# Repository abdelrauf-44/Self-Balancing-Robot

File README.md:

# 🤖 Self-Balancing Robot (ESP32 + MPU6050)

A two-wheeled self-balancing robot based on ESP32 and MPU6050 IMU, implementing PID control to stabilize an inverted pendulum system in real time.
The project focuses on practical control engineering, embedded systems, and electromechanical integration.

# 📌 Project Overview

This project demonstrates the design and implementation of a self-balancing robot using:

Real-time sensor fusion for tilt angle estimation

Closed-loop PID control for balance stabilization

PWM-based DC motor control

Embedded implementation on an ESP32 microcontroller

The robot is capable of maintaining an upright position and recovering from small disturbances.

# 🧩 System Architecture

Main subsystems:

Sensing: MPU6050 (accelerometer + gyroscope)

Control: PID controller running on ESP32

Actuation: Dual DC motors via motor driver

Power: Battery supply with onboard 5V regulation for the motor driver

# 🛠️ Hardware Components

ESP32 super mini 

MPU6050 IMU

DC  Motors (2×)

Motor Driver (L293D)

3D-printed mechanical frame

Battery pack with power switch

# 🔌 Electrical Schematic

The schematic below shows the complete electrical design including:

Power regulation stage

ESP32 GPIO connections

Motor driver interface

# 🧱 Mechanical Design & Assembly

# 🎯 Control Strategy
Angle Estimation

MPU6050 accelerometer and gyroscope data are combined to estimate the robot tilt angle.

Gyroscope data provides short-term accuracy, while accelerometer data corrects long-term drift.

# PID Controller

The controller minimizes the tilt angle error using:

Proportional (P): Immediate correction based on angle error

Integral (I): Reduces steady-state error

Derivative (D): Improves damping and stability

Controller output is converted to PWM signals driving the motors.

# 💻 Software Architecture

Platform: Arduino framework (ESP32)

Main loop:

Read IMU data

Compute tilt angle

Apply PID control

Update motor PWM outputs

Modular structure for easy tuning and testing

# 📡 Features

Real-time balance stabilization

Adjustable PID parameters

Compact embedded implementation

# 🧪 Results & Observations

The robot can balance successfully for short to medium durations.

System stability is sensitive to:

PID tuning

Sensor noise and drift

Loop timing consistency

The project highlights real-world control challenges beyond simulation.

# 🚀 Future Improvements

Implement complementary or Kalman filtering

Add encoder feedback for velocity control

Improve mechanical rigidity

Implement auto-tuning or adaptive control

Wireless parameter tuning and monitoring

# ▶️ How to Run

Upload the firmware to the ESP32 using Arduino IDE

Power the robot on a flat surface

Tune PID parameters carefully

Gradually test balance recovery

⚠️ Start with low motor speed limits to avoid damage.

# 👤 Author

Mohamed Abdelrauf
Electrcial Engineering (UTM) 
Self-Balancing Robot Project

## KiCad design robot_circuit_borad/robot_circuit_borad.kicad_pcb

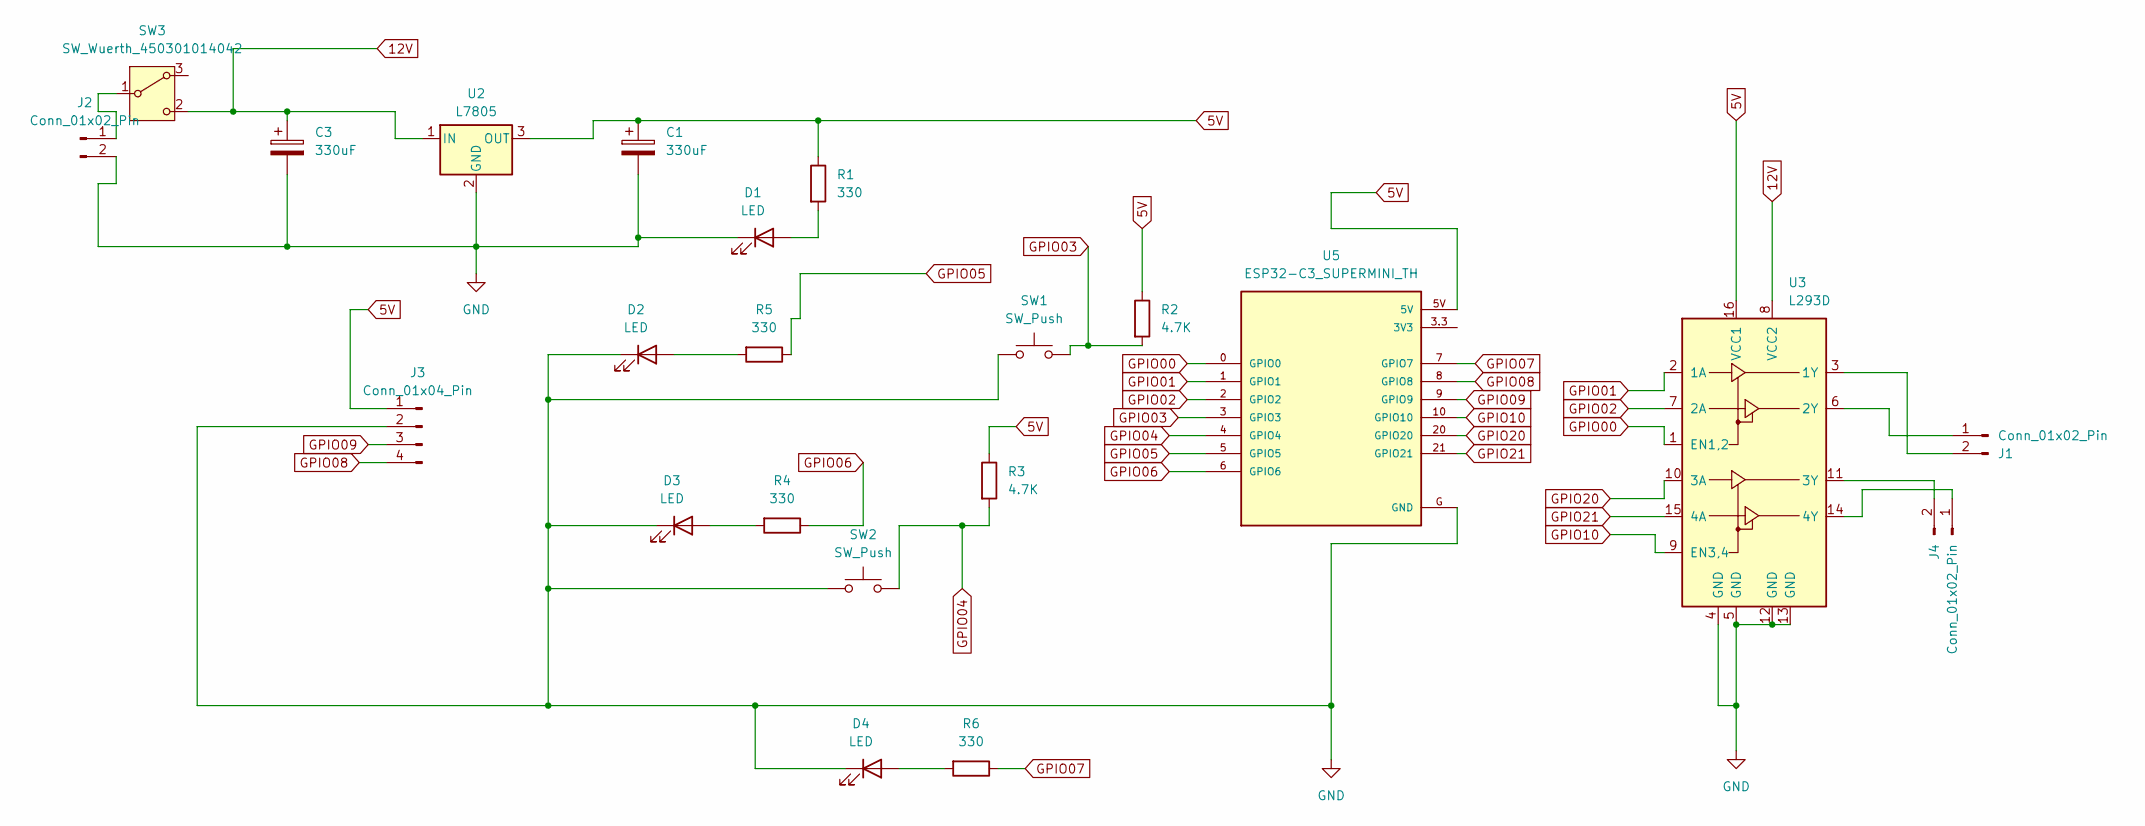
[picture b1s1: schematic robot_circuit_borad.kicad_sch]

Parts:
C1, C3: 330uF; CP_Radial_D6.3mm_P2.50mm
D1, D2, D3, D4: LED; LED_D3.0mm
J1, J2, J4: Conn_01x02_Pin; JST_XH_B2B-XH-A_1x02_P2.50mm_Vertical
J3: Conn_01x04_Pin; PinHeader_1x04_P2.54mm_Vertical
R1, R4, R5, R6: 330; R_Axial_DIN0207_L6.3mm_D2.5mm_P10.16mm_Horizontal
R2, R3: 4.7K; R_Axial_DIN0207_L6.3mm_D2.5mm_P10.16mm_Horizontal
SW1, SW2: SW_Push; SW_TH_Tactile_Omron_B3F-10xx
SW3: SW_Wuerth_450301014042; SW_Slide-03_Wuerth-WS-SLTV_10x2.5x6.4_P2.54mm
U2: L7805; TO-220-3_Vertical
U3: L293D; DIP-16_W7.62mm
U5: ESP32-C3_SUPERMINI_TH; MODULE_ESP32-C3_SUPERMINI

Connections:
5V: C1.1, J3.1, R1.1, R2.1, R3.1, U2.3 (OUT), U3.16 (VCC1), U5.5V
12V: C3.1, SW3.2 (C), U2.1 (IN), U3.8 (VCC2)
GND: C1.2, C3.2, D1.1 (K), D2.1 (K), D3.1 (K), D4.1 (K), J2.2, J3.2, SW1.1, SW2.1, U2.2 (GND), U3.4 (GND), U3.5 (GND), U3.12 (GND), U3.13 (GND), U5.G (GND)
GPIO00: U3.1 (EN1,2), U5.0 (GPIO0)
GPIO01: U3.2 (1A), U5.1 (GPIO1)
GPIO02: U3.7 (2A), U5.2 (GPIO2)
GPIO03: R2.2, SW1.2, U5.3 (GPIO3)
GPIO04: R3.2, SW2.2, U5.4 (GPIO4)
GPIO05: R5.1, U5.5 (GPIO5)
GPIO06: R4.1, U5.6 (GPIO6)
GPIO07: R6.1, U5.7 (GPIO7)
GPIO08: J3.4, U5.8 (GPIO8)
GPIO09: J3.3, U5.9 (GPIO9)
GPIO10: U3.9 (EN3,4), U5.10 (GPIO10)
GPIO20: U3.10 (3A), U5.20 (GPIO20)
GPIO21: U3.15 (4A), U5.21 (GPIO21)
unnamed: D1.2 (A), R1.2
unnamed: D2.2 (A), R5.2
unnamed: D3.2 (A), R4.2
unnamed: D4.2 (A), R6.2
unnamed: J1.1, U3.6 (2Y)
unnamed: J1.2, U3.3 (1Y)
unnamed: J2.1, SW3.1 (B)
unnamed: J4.1, U3.14 (4Y)
unnamed: J4.2, U3.11 (3Y)

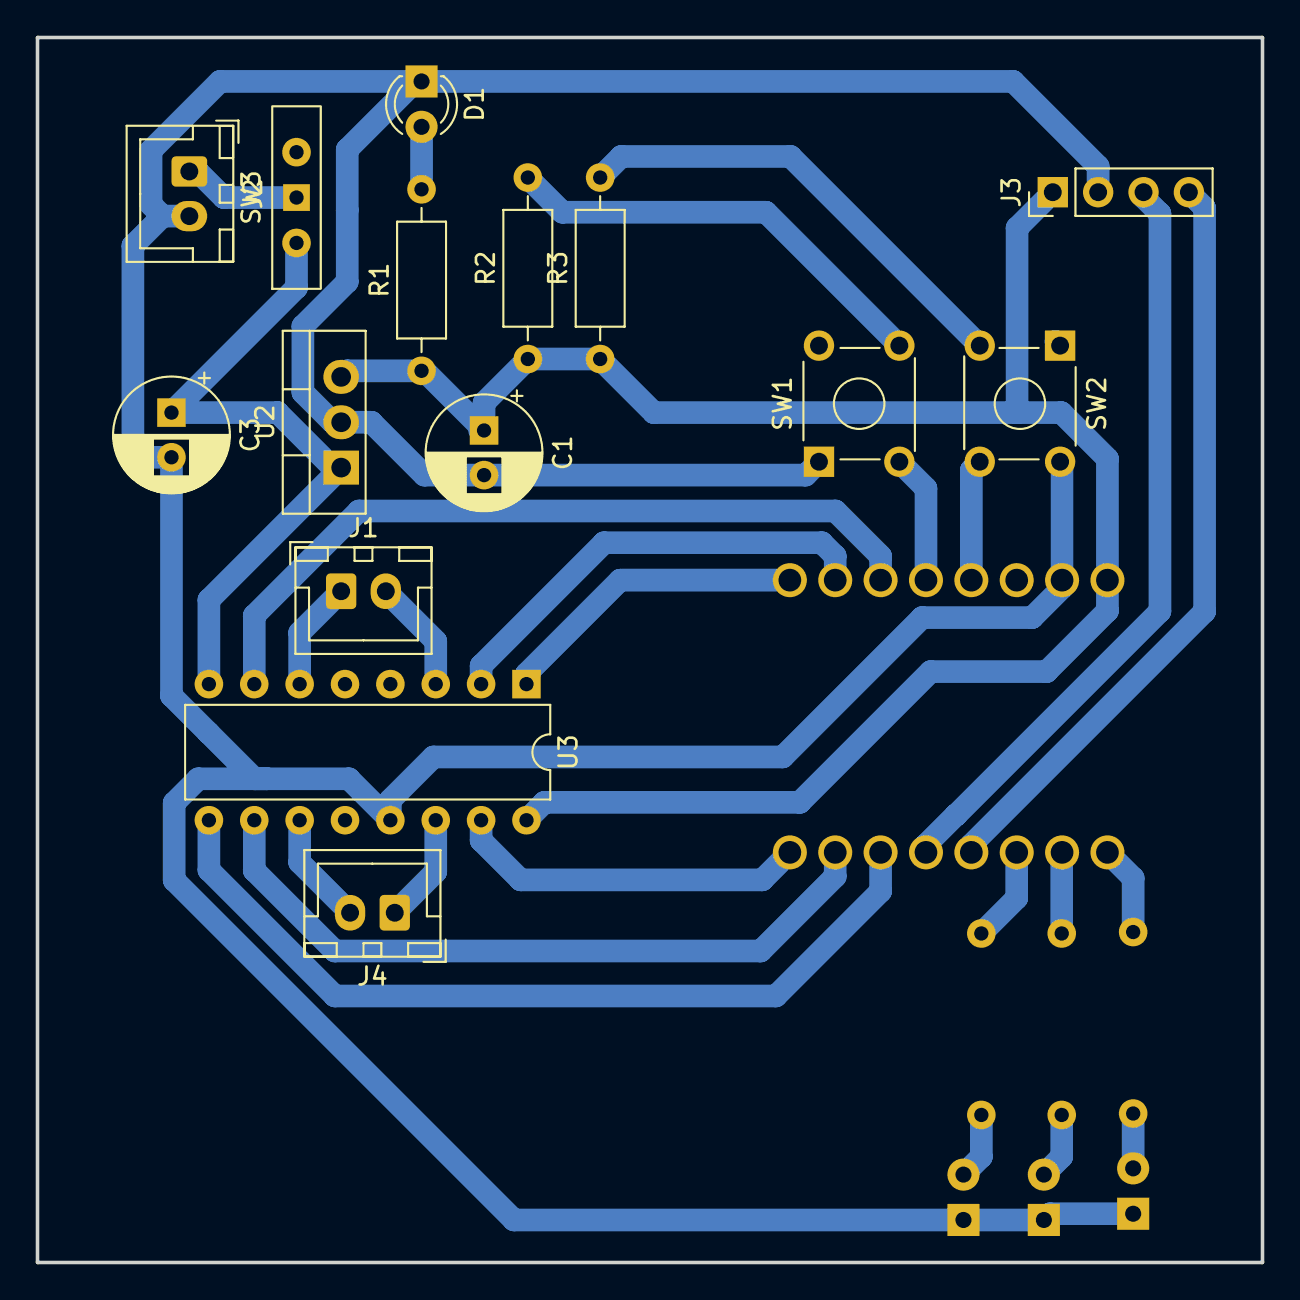
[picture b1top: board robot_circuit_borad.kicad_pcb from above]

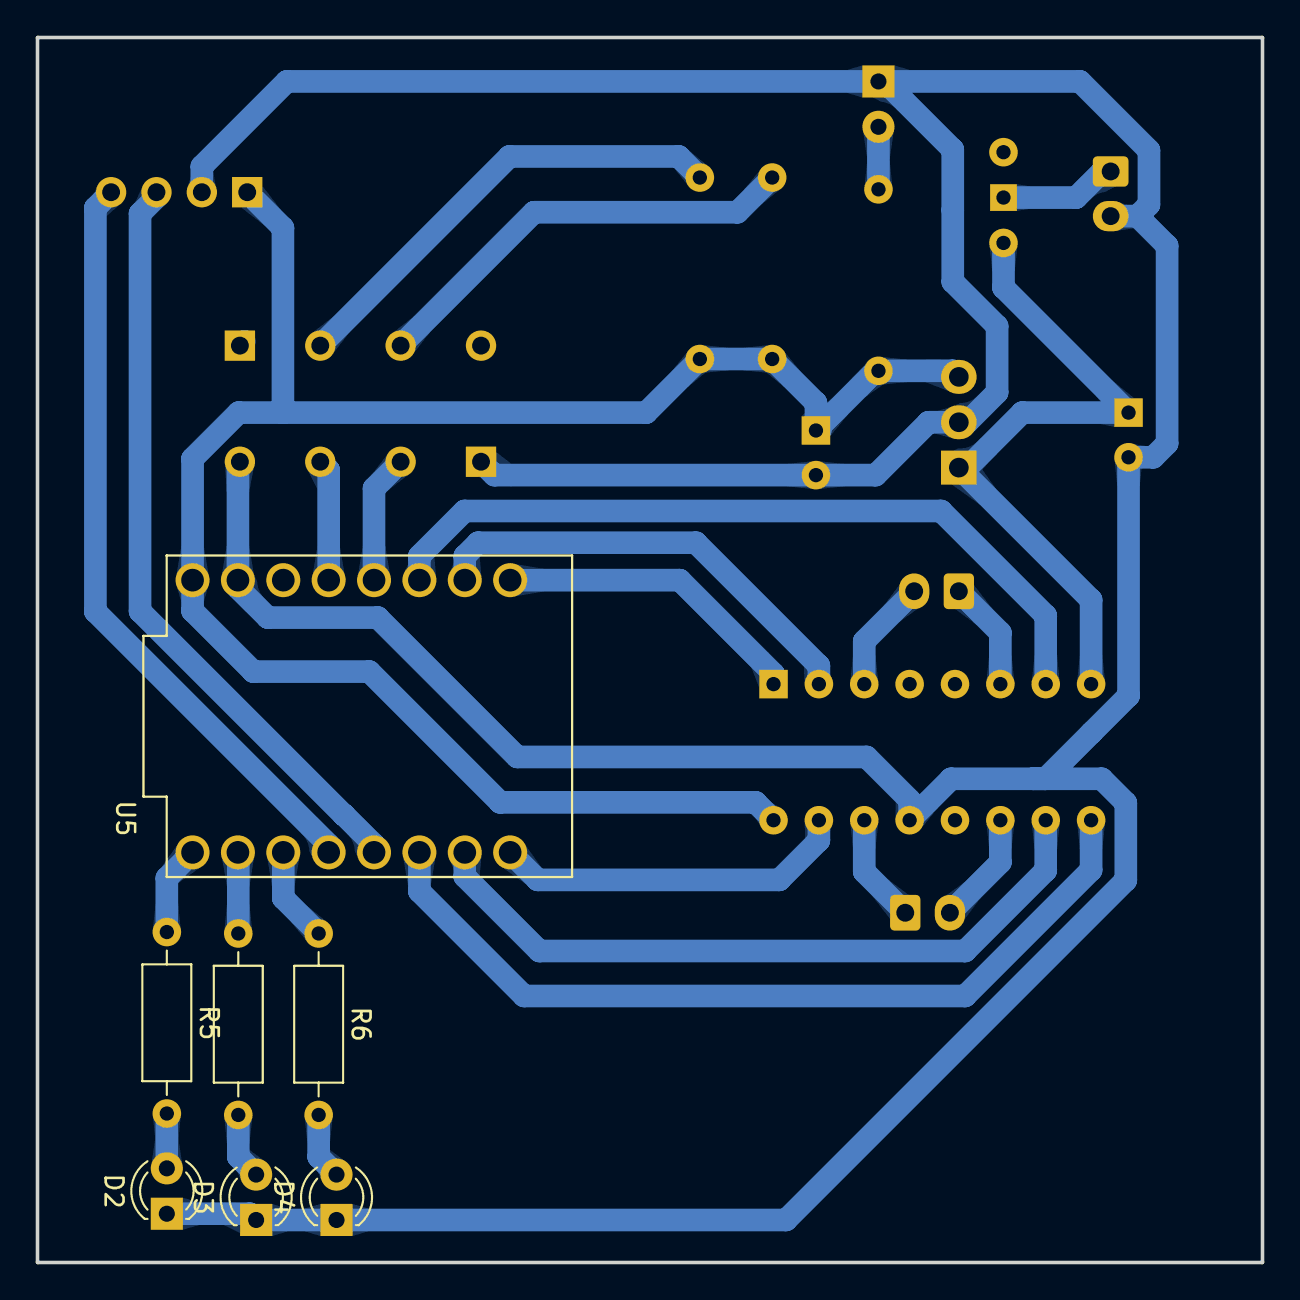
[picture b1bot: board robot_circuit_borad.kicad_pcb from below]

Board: 2 copper layers, 68.6 x 68.6 mm, 22 parts (7 on the bottom side), 25 nets.

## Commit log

2025-12-23 Added design files
2025-12-23 Add README for Self-Balancing Robot project
    Added detailed project description, system architecture, hardware components, control strategy, software architecture, features, results, future improvements, and instructions for running the self-ba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
2025-12-23 Added images of the schematics and the robot base
2025-12-23 Revise hardware components and add images
    Updated hardware components and images in the README.
2025-12-23 add robot base and robot assemble images
2025-12-23 Refactor README.md with proper headings
    Updated README.md to improve formatting and structure with appropriate headings.
